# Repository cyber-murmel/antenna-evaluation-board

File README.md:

# Antenna Evaluation Board
Panel of test coupons with multiple antenna designs.

For KiCad *Version: 7.0.1, release build*

Browse the files on [KiCanvas](https://kicanvas.org/?github=https://github.com/cyber-murmel/antenna-evaluation-board/tree/main/source/antenna-evaluation-board) - by [Stargirl Flowers](https://github.com/theacodes)

## Directory Structure
| directory  | content                                                              |
|------------|----------------------------------------------------------------------|
| source     | KiCad project directories                                            |
| production | fabrication files (Gerber, BOM, placement)                           |
| exports    | schematic and layout plots, board 3D model and renderings            |
| datasheets | component datasheets                                                 |
| assets     | board setups, component 3D models, logos                             |
| scripts    | BOM export plugins, miscellaneous helper scripts for file conversion |
| hooks      | git hooks, for example for automatic documentation export            |

## Automation
This repository contains a Makefile that automates PDF and Gerber export.

### Requirements
Apart from [KiCad 7](#kicad-version) this requires some additional software.

The Makefile calls a Python script that makes use of [sexptdata](https://pypi.org/project/sexpdata/) to parse KiCad files.
Install [Poetry](https://python-poetry.org/) and run `poetry shell` followed by `poetry install` in the root of this repositoryto set up a virtual environment with the required package(s). To re-enter this environment, simply run `poetry shell` in the root of this repository.

For PDF export you additonally need to install [Poppler](https://poppler.freedesktop.org/).
Gerber export requires [zip](https://infozip.sourceforge.net/).

#### Nix(OS)
If you are using the Nix package manager, you can enter a development environment
with KiCad and all other software by running `nix-shell` in the root of this
repository.

### Export
To export all PDFs and production files, simply run
```shell
make
```
PDFs and production files are exported automatically when you `git commit`, if you have
[Git Hooks](#installing-git-hooks-optional) set up.

### Installing Git Hooks (optional)
The [hooks](hooks) directory contains client-side [git hooks](https://git-scm.com/book/en/v2/Customizing-Git-Git-Hooks).
Currently only the pre-commit hook is used to automatically export plots.

To enable the hooks locally, run the following in the root of the repository.
```shell
git config core.hooksPath ./hooks
```

## KiCad Version
Version information of the KiCad used to generate the files.
```
[nix-shell:~/repos/kicad-template]$ kicad-cli version --format about

Application: kicad-cli x86_64 on x86_64

Version: 7.0.1, release build

Libraries:
        wxWidgets 3.2.2
        FreeType 2.12.1
        HarfBuzz 6.0.0
        FontConfig 2.14.0
        libcurl/7.87.0 OpenSSL/3.0.8 zlib/1.2.13 brotli/1.0.9 zstd/1.5.2 libidn2/2.3.2 libssh2/1.10.0 nghttp2/1.51.0

Platform: , 64 bit, Little endian, wxBase, , wayland

Build Info:
        Date: Jan  1 1980 00:00:00
        wxWidgets: 3.2.2 (wchar_t,wx containers) GTK+ 0.0
        Boost: 1.79.0
        OCC: 7.6.2
        Curl: 7.87.0
        ngspice: 37
        Compiler: GCC 12.2.0 with C++ ABI 1017

Build settings:
        KICAD_USE_EGL=ON
        KICAD_SPICE=ON
```

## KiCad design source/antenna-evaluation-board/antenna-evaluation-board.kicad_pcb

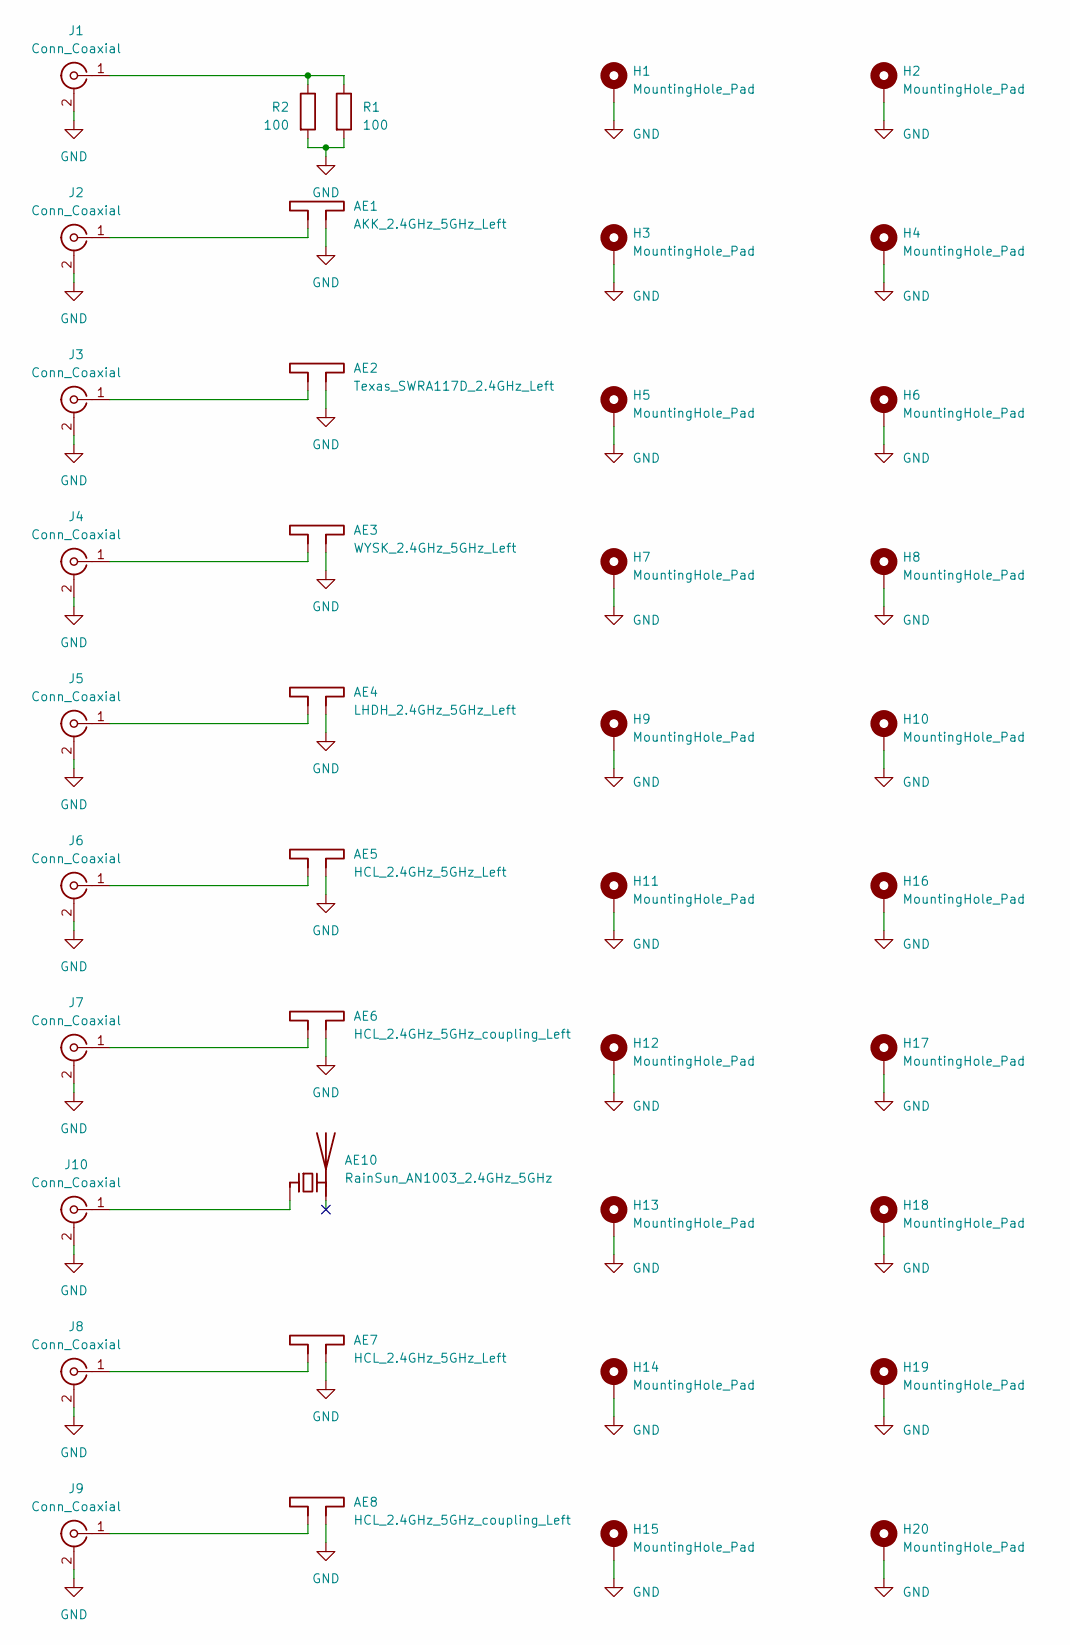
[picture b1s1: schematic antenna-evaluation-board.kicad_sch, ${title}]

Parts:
AE1: AKK_2.4GHz_5GHz_Left
AE2: Texas_SWRA117D_2.4GHz_Left
AE3: WYSK_2.4GHz_5GHz_Left
AE4: LHDH_2.4GHz_5GHz_Left
AE5, AE7: HCL_2.4GHz_5GHz_Left
AE6, AE8: HCL_2.4GHz_5GHz_coupling_Left
AE10: RainSun_AN1003_2.4GHz_5GHz
H1, H2, H3, H4, H5, H6, H7, H8, H9, H10, H11, H12, H13, H14, H15, H16, H17, H18, H19, H20: MountingHole_Pad; MountingHole_3mm_Pad_Via
J1, J2, J3, J4, J5, J6, J7, J8, J9, J10: Conn_Coaxial; SMA_Molex_73251-2120_EdgeMount_Horizontal
R1, R2: 100; R_0402_1005Metric

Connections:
GND: AE1.2, AE2.2, AE3.2, AE4.2, AE5.2, AE6.2, AE7.2, AE8.2, H1.1, H2.1, H3.1, H4.1, H5.1, H6.1, H7.1, H8.1, H9.1, H10.1, H11.1, H12.1, H13.1, H14.1, H15.1, H16.1, H17.1, H18.1, H19.1, H20.1, J1.2 (Ext), J2.2 (Ext), J3.2 (Ext), J4.2 (Ext), J5.2 (Ext), J6.2 (Ext), J7.2 (Ext), J8.2 (Ext), J9.2 (Ext), J10.2 (Ext), R1.2, R2.2
unnamed: AE10.1 (FEED), J10.1 (In)
unnamed: J1.1 (In), R1.1, R2.1
unnamed: AE1.1, J2.1 (In)
unnamed: AE2.1, J3.1 (In)
unnamed: AE3.1, J4.1 (In)
unnamed: AE4.1, J5.1 (In)
unnamed: AE5.1, J6.1 (In)
unnamed: AE6.1, J7.1 (In)
unnamed: AE7.1, J8.1 (In)
unnamed: AE8.1, J9.1 (In)

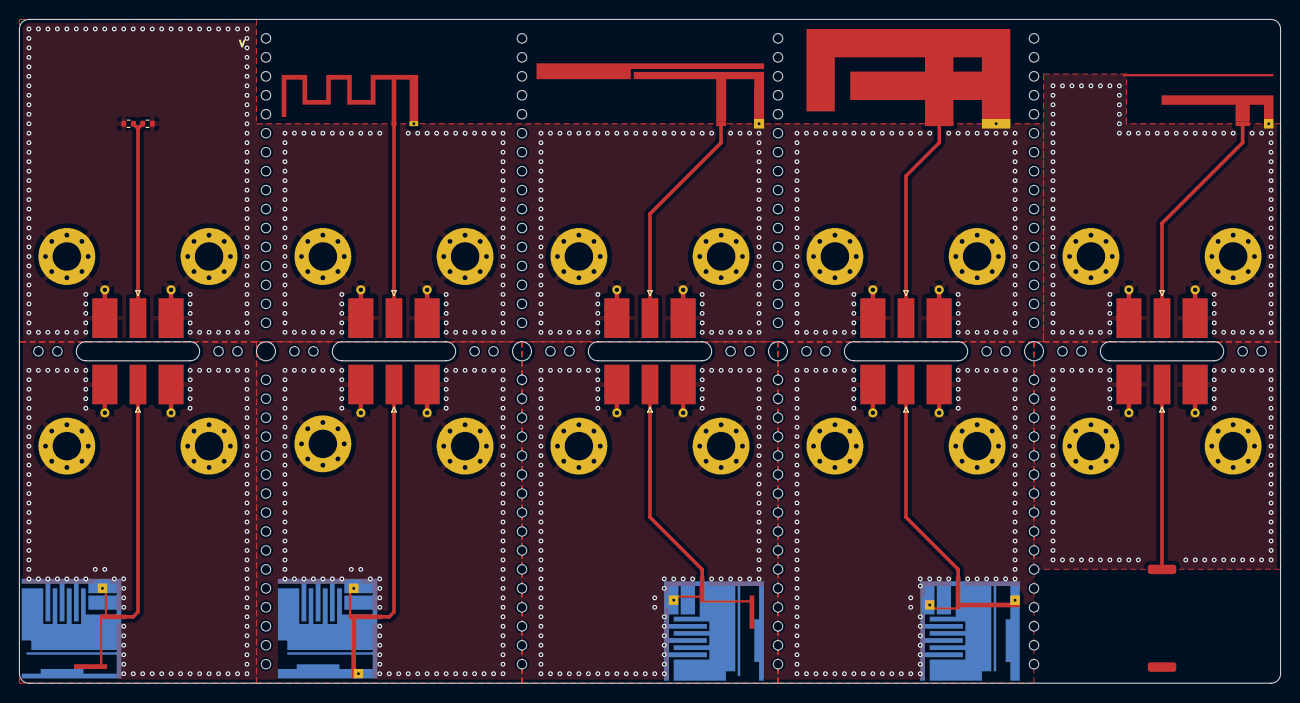
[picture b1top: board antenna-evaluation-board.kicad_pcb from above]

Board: 4 copper layers, 133.0 x 70.0 mm, 41 parts (0 on the bottom side), 11 nets.

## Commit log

2023-05-05 set corretct project name
2023-05-05 finished schematic and layout
2023-05-05 add production files
2023-05-05 updated readme; added renderings
2023-05-09 use tons of drils instead of v cuts
